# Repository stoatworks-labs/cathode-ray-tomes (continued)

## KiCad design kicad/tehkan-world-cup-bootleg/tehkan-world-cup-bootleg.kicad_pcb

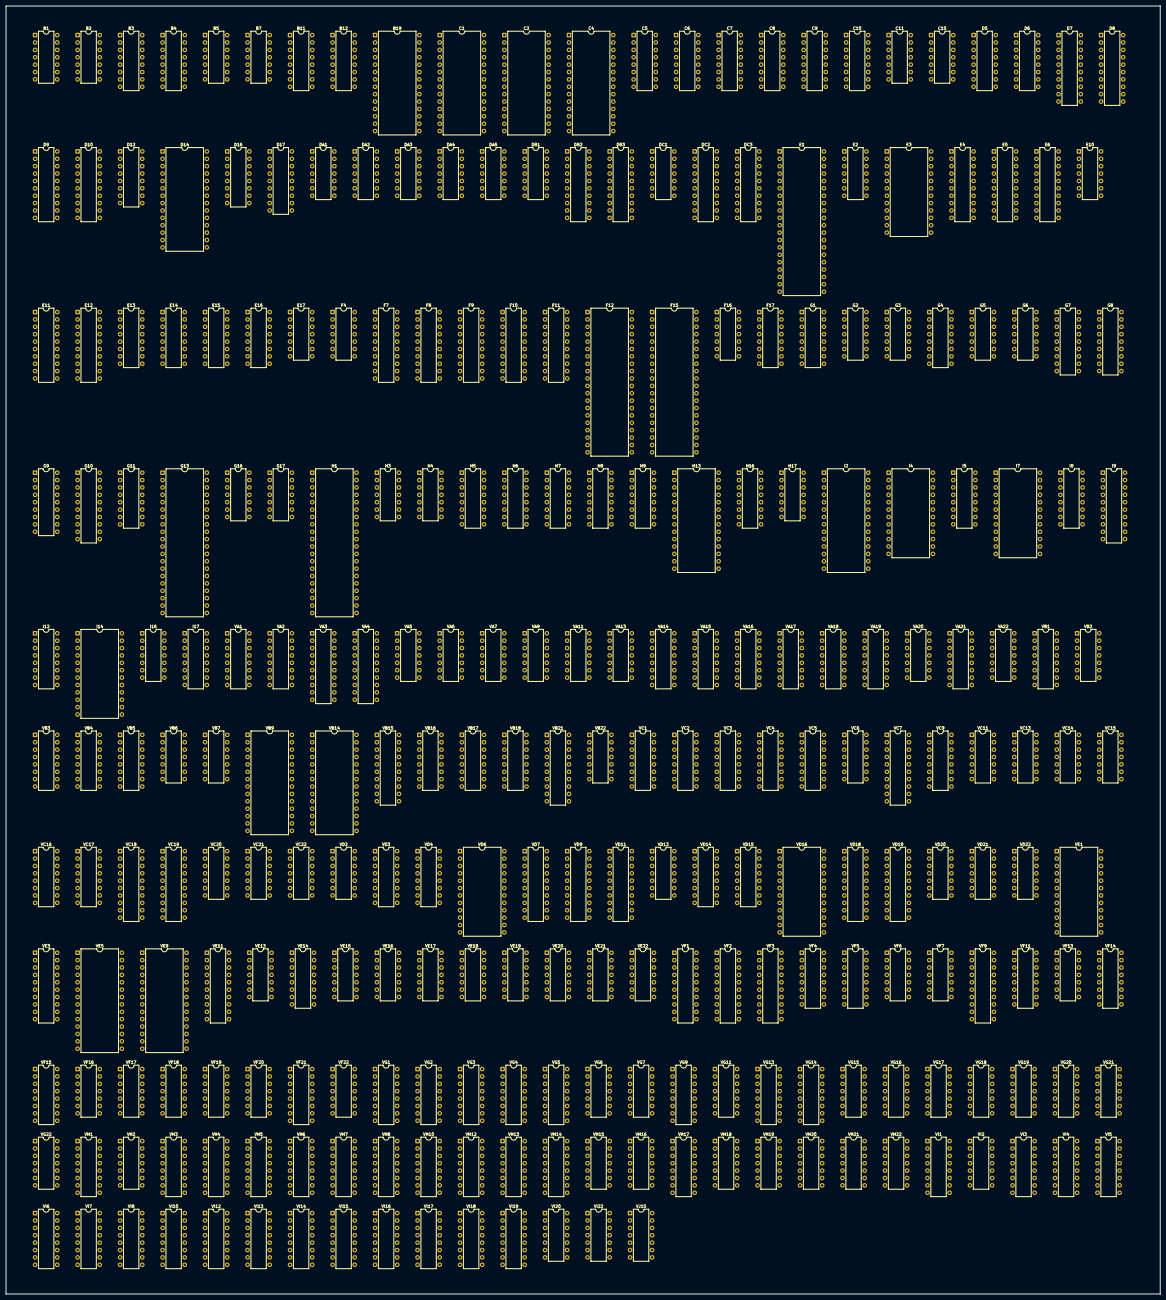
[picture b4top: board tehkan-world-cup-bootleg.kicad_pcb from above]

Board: 2 copper layers, 397.1 x 443.1 mm, 262 parts (0 on the bottom side), 1009 nets, no tracks yet.

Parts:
B1, B2: 74LS74; DIP-14_W7.62mm
B3, B4, B11, B12: 74LS367; DIP-16_W7.62mm
B5, B7: 74LS04; DIP-14_W7.62mm
B19: 27128; DIP-28_W15.24mm
C1, C2, C4: 27128; DIP-28_W15.24mm
C5: 74LS138; DIP-16_W7.62mm
C6: 74LS139; DIP-16_W7.62mm
C7, C8, C9, C10: 74LS157; DIP-16_W7.62mm
C11: 74LS74; DIP-14_W7.62mm
C15: LM324; DIP-14_W7.62mm
D5: 74LS138; DIP-16_W7.62mm
D6: 74LS139; DIP-16_W7.62mm
D7, D8, D9, D10: 74LS244; DIP-20_W7.62mm
D12: 74LS174; DIP-16_W7.62mm
D14: 27128; DIP-28_W15.24mm
D16: 74LS157; DIP-16_W7.62mm
D17: OKI-M5205; DIP-18_W7.62mm
DA1, DA2, DA3: 74LS00; DIP-14_W7.62mm
DA4, DA5: 74LS74; DIP-14_W7.62mm
DB1: 74LS32; DIP-14_W7.62mm
DB2: 74LS373; DIP-20_W7.62mm
DB3: 74LS245; DIP-20_W7.62mm
DC1: 74LS32; DIP-14_W7.62mm
DC2: 74LS373; DIP-20_W7.62mm
DC3: 74LS245; DIP-20_W7.62mm
E1: Z80CPU; DIP-40_W15.24mm
E2, E10: 74LS08; DIP-14_W7.62mm
E3: HM6116P-3; DIP-24_W15.24mm
E4: 74LS245; DIP-20_W7.62mm
E5, E6: 74LS244; DIP-20_W7.62mm
E11, E12: 74LS374; DIP-20_W7.62mm
E13, E14, E15, E16: 74LS191; DIP-16_W7.62mm
E17: 74LS32; DIP-14_W7.62mm
F4: 74LS32; DIP-14_W7.62mm
F7, F8, F9: 74LS273; DIP-20_W7.62mm
F10, F11: 74LS245; DIP-20_W7.62mm
F12, F15: YM2149; DIP-40_W15.24mm
F16: 74LS02; DIP-14_W7.62mm
F17: 74LS367; DIP-16_W7.62mm
G1: 74LS139; DIP-16_W7.62mm
G2, G17: 74LS32; DIP-14_W7.62mm
G3: 74LS08; DIP-14_W7.62mm
G4: 74LS367; DIP-16_W7.62mm
G5: 74LS11; DIP-14_W7.62mm
G6: 74LS74; DIP-14_W7.62mm
G7, G8, G9: MN2114; DIP-18_W7.62mm
G10: 74LS245; DIP-20_W7.62mm
G11: 74LS138; DIP-16_W7.62mm
G13: Z80CPU; DIP-40_W15.24mm
G16: 74LS02; DIP-14_W7.62mm
H1: Z80CPU; DIP-40_W15.24mm
H3, H17: 74LS04; DIP-14_W7.62mm
H4: 74LS74; DIP-14_W7.62mm
H5, H8: 74LS367; DIP-16_W7.62mm
H6, H7: 74LS157; DIP-16_W7.62mm
H9: 74LS138; DIP-16_W7.62mm
H13: 27128; DIP-28_W15.24mm
H16: 74LS139; DIP-16_W7.62mm
I2: 27256; DIP-28_W15.24mm
I4, I7, I14: HM6116P-3; DIP-24_W15.24mm
I5: 74LS157; DIP-16_W7.62mm
I8: 74LS367; DIP-16_W7.62mm
I9: 74LS245; DIP-20_W7.62mm
I12, I17: 74LS257; DIP-16_W7.62mm
I16: 74LS74; DIP-14_W7.62mm
VA1, VA2: 74LS161; DIP-16_W7.62mm
VA3, VA4: 74LS273; DIP-20_W7.62mm
VA5, VA13: 74LS32; DIP-14_W7.62mm
VA6: 74LS86; DIP-14_W7.62mm
VA7, VA9: 74LS11; DIP-14_W7.62mm
VA11, VA22: 74LS08; DIP-14_W7.62mm
VA14: 74LS139; DIP-16_W7.62mm
VA15, VA16, VA17, VA18, VA19: 74LS153; DIP-16_W7.62mm
VA20: 74LS25; DIP-14_W7.62mm
VA21: 74LS157; DIP-16_W7.62mm
VB1: 74LS161; DIP-16_W7.62mm
VB2: 74LS74; DIP-14_W7.62mm
VB3, VB4, VB5: 74LS283; DIP-16_W7.62mm
VB6, VB7: 74LS86; DIP-14_W7.62mm
VB9, VB14: 27256; DIP-28_W15.24mm
VB15, VB21: 74LS273; DIP-20_W7.62mm
VB16, VB17: 74LS157; DIP-16_W7.62mm
VB18: 74LS174; DIP-16_W7.62mm
VB22: 74LS32; DIP-14_W7.62mm
VC1, VC2, VC4, VC5, VC16, VC17: 74LS157; DIP-16_W7.62mm
VC3: 74LS283; DIP-16_W7.62mm
VC6: 74LS08; DIP-14_W7.62mm
VC7, VC19: 74LS273; DIP-20_W7.62mm
VC9: 74LS174; DIP-16_W7.62mm
VC11, VC20: 74LS86; DIP-14_W7.62mm
VC13, VC14: 74LS74; DIP-14_W7.62mm
VC15, VC21, VC22: 74LS32; DIP-14_W7.62mm
VC18: 74LS245; DIP-20_W7.62mm
VD2, VD21: 74LS74; DIP-14_W7.62mm
VD3, VD4: 74LS157; DIP-16_W7.62mm
VD6, VD16: HM6116P-3; DIP-24_W15.24mm
VD7, VD9, VD18, VD19: 74LS273; DIP-20_W7.62mm
VD11: 74LS245; DIP-20_W7.62mm
VD13: 74LS00; DIP-14_W7.62mm
VD14: 74LS175; DIP-16_W7.62mm
VD15: 74LS283; DIP-16_W7.62mm
VD20: 74LS86; DIP-14_W7.62mm
VD22: 74LS08; DIP-14_W7.62mm
VE1: HM6116P-3; DIP-24_W15.24mm
VE3, VE11: 74LS273; DIP-20_W7.62mm
VE5, VE9: 27256; DIP-28_W15.24mm
VE13, VE15: 74LS86; DIP-14_W7.62mm
VE14: 74LS139; DIP-16_W7.62mm
VE16, VE17, VE18: 74LS74; DIP-14_W7.62mm
VE19: 74LS02; DIP-14_W7.62mm
VE20, VE22: 74LS32; DIP-14_W7.62mm
VE21: 74LS04; DIP-14_W7.62mm
VF1, VF2: 74LS245; DIP-20_W7.62mm
VF3, VF9: 74LS273; DIP-20_W7.62mm
VF4, VF5: 74LS161; DIP-16_W7.62mm
VF6, VF7, VF20: 74LS08; DIP-14_W7.62mm
VF11: 74LS157; DIP-16_W7.62mm
VF13: 74LS86; DIP-14_W7.62mm
VF14: 74LS298; DIP-16_W7.62mm
VF15: 74LS194; DIP-16_W7.62mm
VF16: 74LS32; DIP-14_W7.62mm
VF17: 74LS30; DIP-14_W7.62mm
VF18, VF19, VF22: 74LS74; DIP-14_W7.62mm
VF21: 74LS175; DIP-16_W7.62mm
VG1, VG2, VG3: 74LS161; DIP-16_W7.62mm
VG4, VG5, VG13: 74LS157; DIP-16_W7.62mm
VG6, VG7, VG18: 74LS08; DIP-14_W7.62mm
VG9: 74LS174; DIP-16_W7.62mm
VG11: 74LS25; DIP-14_W7.62mm
VG14: 74LS298; DIP-16_W7.62mm
VG15: 74LS10; DIP-14_W7.62mm
VG16: 74LS27; DIP-14_W7.62mm
VG17: 74LS20; DIP-14_W7.62mm
VG19, VG21, VG22: 74LS74; DIP-14_W7.62mm
VG20: 74LS04; DIP-14_W7.62mm
VH1: 74LS161; DIP-16_W7.62mm
VH2, VH15, VH16, VH18, VH19: 74LS86; DIP-14_W7.62mm
VH3, VH4, VH5: 74LS157; DIP-16_W7.62mm
VH6, VH7, VH8, VH10, VH12, VH13, VH14: DIP-16_W7.62mm
VH17: 74LS367; DIP-16_W7.62mm
VH20: 74LS00; DIP-14_W7.62mm
VH21: 74LS393; DIP-14_W7.62mm
VH22: 74LS04; DIP-14_W7.62mm
VI1, VI15, VI16, VI18, VI19: 74LS161; DIP-16_W7.62mm
VI2: 74LS86; DIP-14_W7.62mm
VI3, VI4, VI5: 74LS157; DIP-16_W7.62mm
VI6, VI7, VI8, VI10, VI12, VI13, VI14: DIP-16_W7.62mm
VI17: 74LS367; DIP-16_W7.62mm
VI20: 74LS107; DIP-14_W7.62mm
VI22: 4069; DIP-14_W7.62mm
VJ15: 74LS04; DIP-14_W7.62mm

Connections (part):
/CLK4: H3.3, H3.13, VH22.2
/HB0: H17.5, H17.9
/PXLCLK: F7.11, F8.11, F9.11, VE20.8
/cpu board/4MCK: DA4.3, DA4.11, DA5.3, DA5.11
/cpu board/DB0: B1.2, B1.12, B2.2, B2.12, B3.11, B4.11, B11.13, B12.3, D7.3, D8.3, D9.3, D10.3, DB2.12, DB3.11, E4.11, E5.9, E6.9, E11.3, E12.2
/cpu board/DB1: B3.13, B4.13, B11.9, B12.5, D7.5, D8.5, D9.5, D10.5, DB2.9, DB3.12, E4.12, E5.12, E6.12, E11.4, E12.5
/cpu board/DB2: B3.7, B4.7, B11.11, B12.7, D7.7, D8.7, D9.7, D10.7, DB2.15, DB3.13, E4.13, E5.7, E6.7, E11.7, E12.6
/cpu board/DB3: B3.5, B4.5, B11.3, B12.9, D7.9, D8.9, D9.9, D10.9, DB2.6, DB3.14, E4.14, E5.14, E6.14, E11.8, E12.9
/cpu board/DB4: B4.3, B11.5, D7.12, D8.12, D9.12, D10.12, DB2.16, DB3.15, E4.15, E5.5, E6.5, E11.13, E12.12
/cpu board/DB5: B4.9, B11.7, D7.14, D8.14, D9.14, D10.14, DB2.5, DB3.16, E4.16, E5.16, E6.16, E11.14, E12.15
/cpu board/DB6: D7.16, D8.16, D9.16, D10.16, DB2.19, DB3.17, E4.17, E5.3, E6.3, E11.17, E12.16
/cpu board/DB7: D7.18, D8.18, D9.18, D10.18, DB2.2, DB3.18, E4.18, E5.18, E6.18, E11.18, E12.19
/cpu board/DD0: DB2.13, DB3.9, DC2.13, DC3.9, F10.9, G10.2, I9.2, VA3.3, VA4.3, VC13.2, VC18.9, VD11.9, VF1.9
/cpu board/DD1: DB2.8, DB3.8, DC2.8, DC3.8, F10.8, G10.3, I9.3, VA3.4, VA4.4, VC18.8, VD11.8, VF1.8
/cpu board/DD2: DB2.14, DB3.7, DC2.14, DC3.7, F10.7, G10.4, I9.4, VA3.7, VA4.7, VC18.7, VD11.7, VF1.7
/cpu board/DD3: DB2.7, DB3.6, DC2.7, DC3.6, F10.6, G10.5, I9.5, VA3.8, VA4.8, VC18.6, VD11.6, VF1.6
/cpu board/DD4: DB2.17, DB3.5, DC2.17, DC3.5, F10.5, G10.6, I9.6, VA3.13, VA4.13, VC18.5, VD11.5, VF1.5
/cpu board/DD5: DB2.4, DB3.4, DC2.4, DC3.4, F10.4, G10.7, I9.7, VA3.14, VA4.14, VC18.4, VD11.4, VF1.4
/cpu board/DD6: DB2.18, DB3.3, DC2.18, DC3.3, F10.3, G10.8, I9.8, VA3.17, VA4.17, VC18.3, VD11.3, VF1.3
/cpu board/DD7: DB2.3, DB3.2, DC2.3, DC3.2, F10.2, G10.9, I9.9, VA3.18, VA4.18, VC18.2, VD11.2, VF1.2
/cpu board/DISP: F7.1, F8.1, F9.1, VF20.11
/cpu board/DS0: DC2.12, DC3.11, H1.14, I2.11, I4.9
/cpu board/DS1: DC2.9, DC3.12, H1.15, I2.12, I4.10
/cpu board/DS2: DC2.15, DC3.13, H1.12, I2.13, I4.11
/cpu board/DS3: DC2.6, DC3.14, H1.8, I2.15, I4.13
/cpu board/DS4: DC2.16, DC3.15, H1.7, I2.16, I4.14
/cpu board/DS5: DC2.5, DC3.16, H1.9, I2.17, I4.15
/cpu board/DS6: DC2.19, DC3.17, H1.10, I2.18, I4.16
/cpu board/DS7: DC2.2, DC3.18, H1.13, I2.19, I4.17
/cpu board/HFLIP: B2.9, VC6.12, VC20.1, VC20.9, VE15.12, VG18.12
/cpu board/IO0: C6.4, D10.1, D10.19
/cpu board/IO1: C6.5, D9.1, D9.19
/cpu board/IO2: B12.1, C6.6
/cpu board/IO3: B11.1, B11.15, C6.7
/cpu board/IO4: D6.4, D8.1, D8.19
/cpu board/IO5: D6.5, D7.1, D7.19
/cpu board/IO7: B4.1, B4.15, D6.7
/cpu board/IO/~DIP1: B3.1, B3.15, D5.7
/cpu board/IO/~DIP2: D5.11, E6.1, E6.19
/cpu board/IO/~DIP3: D5.10, E5.1, E5.19
/cpu board/MA0: C6.2, C6.14, D6.2, D6.14, H5.3, H7.2
/cpu board/MA1: C6.3, C6.13, D6.3, D6.13, H5.5, H7.5
/cpu board/MA2: H5.11, H7.11
/cpu board/MA3: H5.13, H7.14
/cpu board/MA4: C5.1, D5.1, H5.7, H6.2
/cpu board/MA5: C5.2, D5.2, H5.9, H6.5
/cpu board/MA6: C5.3, D5.3, G4.13, H6.11
/cpu board/MA7: G4.3, H6.14
/cpu board/MA8: G4.5, I5.2
/cpu board/MA9: G4.7, I5.5
/cpu board/MA10: G4.9, I5.11
/cpu board/MxC8: G3.13, H9.14, I12.2, VA9.5
/cpu board/MxD0: H9.13, I12.5, VA9.4
/cpu board/MxD8: H9.12, I12.11, VA7.5
/cpu board/MxE0: H9.11, I12.14, VA7.4
/cpu board/MxE8: H9.10, I17.2, VA7.3
/cpu board/PA0: G7.5, G8.5, G9.5, VA15.7
/cpu board/PA1: G7.6, G8.6, G9.6, VA15.9
/cpu board/PA2: G7.7, G8.7, G9.7, VA16.7
/cpu board/PA3: G7.4, G8.4, G9.4, VA16.9
/cpu board/PA4: G7.3, G8.3, G9.3, VA17.7
/cpu board/PA5: G7.2, G8.2, G9.2, VA17.9
/cpu board/PA6: G7.1, G8.1, G9.1, VA18.7
/cpu board/PA7: G7.17, G8.17, G9.17, VA18.9
/cpu board/PA8: G7.16, G8.16, G9.16, VA19.7
/cpu board/PA9: G7.15, G8.15, G9.15, VA19.9
/cpu board/SA0: H1.30, H7.3, I2.10, I4.8
/cpu board/SA1: H1.31, H7.6, I2.9, I4.7
/cpu board/SA2: H1.32, H7.10, I2.8, I4.6
/cpu board/SA3: H1.33, H7.13, I2.7, I4.5
/cpu board/SA4: H1.34, H6.3, I2.6, I4.4
/cpu board/SA5: H1.35, H6.6, I2.5, I4.3
/cpu board/SA6: H1.36, H6.10, I2.4, I4.2
/cpu board/SA7: H1.37, H6.13, I2.3, I4.1
/cpu board/SA8: H1.38, I2.25, I4.23, I5.3
/cpu board/SA9: H1.39, I2.24, I4.22, I5.6
/cpu board/SA10: H1.40, I2.21, I4.19, I5.10
/cpu board/SA11: G11.1, H1.1, I2.23
/cpu board/SA12: G11.2, H1.2, I2.2
/cpu board/SA13: G11.3, H1.3, I2.26
/cpu board/SA14: G1.14, H1.4, I2.27
/cpu board/SA15: G1.13, H1.5
/cpu board/SHAB0: H8.5, VA14.2, VC1.2, VC5.2, VC17.2, VC21.10, VE21.13
/cpu board/SHAB1: H8.9, VA14.3, VA15.6, VC1.5, VC5.5, VC17.5
/cpu board/SHAB2: H8.13, VA15.10, VC1.11, VC5.11, VC17.11
/cpu board/SHAB3: H8.11, VA16.6, VC1.14, VC5.14, VC17.14
/cpu board/SHAB4: H8.3, VA16.10, VC2.2, VC4.2, VC16.2
/cpu board/SHAB5: H8.7, VA17.6, VC2.5, VC4.5, VC16.5
/cpu board/SHAB6: I8.3, VA17.10, VC2.11, VC4.11, VC16.11
/cpu board/SHAB7: I8.11, VA18.6, VC2.14, VC4.14, VC16.14
/cpu board/SHAB8: I8.5, VA18.10, VB17.2, VD3.2, VD4.2
/cpu board/SHAB9: I8.9, VA19.6, VB17.5, VD3.5, VD4.5
/cpu board/SHAB10: I8.7, VA19.10, VB17.11, VD4.11, VD13.4, VE20.13
/cpu board/SH~RD: F10.1, G10.1, I8.13, VA22.2, VB17.14, VC18.1, VD3.11, VD4.14, VD11.1, VF1.1
/cpu board/SSD0: I12.7, VE21.1, VE22.2, VE22.4
/cpu board/SSD8: I12.9, VC21.2, VC22.1, VE21.11
/cpu board/SSE0: I12.12, VC15.9, VD13.12
/cpu board/SSE8: I17.4, VE19.8, VE20.12
/cpu board/SxC8: G3.10, G11.14, I12.3, VA7.9
/cpu board/SxD0: G11.13, I12.6, VA7.10
/cpu board/SxD8: G11.12, I12.10, VA7.2
/cpu board/SxE0: G11.11, I12.13, VA7.1
/cpu board/SxE8: G11.10, I17.3, VA7.13
/cpu board/VBL: I16.3, VD22.10, VD22.12, VF20.12, VG21.9
/cpu board/VFLIP: B2.5, VA6.1, VG18.5
/cpu board/WDOG: D5.9, VH20.2
/cpu board/main CPU/A0: C1.10, C2.10, C4.10, E1.30, E3.8, H5.2
/cpu board/main CPU/A1: C1.9, C2.9, C4.9, E1.31, E3.7, H5.4
/cpu board/main CPU/A2: C1.8, C2.8, C4.8, E1.32, E3.6, H5.12
/cpu board/main CPU/A3: C1.7, C2.7, C4.7, E1.33, E3.5, H5.14
/cpu board/main CPU/A4: C1.6, C2.6, C4.6, E1.34, E3.4, H5.6
/cpu board/main CPU/A5: C1.5, C2.5, C4.5, E1.35, E3.3, H5.10
/cpu board/main CPU/A6: C1.4, C2.4, C4.4, E1.36, E3.2, G4.14
/cpu board/main CPU/A7: C1.3, C2.3, C4.3, E1.37, E3.1, G4.2
/cpu board/main CPU/A8: C1.25, C2.25, C4.25, E1.38, E3.23, G4.4
/cpu board/main CPU/A9: C1.24, C2.24, C4.24, E1.39, E3.22, G4.6
/cpu board/main CPU/A10: C1.21, C2.21, C4.21, E1.40, E3.19, G4.10
/cpu board/main CPU/A11: C1.23, C2.23, C4.23, E1.1, H9.1
/cpu board/main CPU/A12: C1.2, C2.2, C4.2, E1.2, H9.2
/cpu board/main CPU/A13: C1.26, C2.26, C4.26, E1.3, H9.3
/cpu board/main CPU/A14: E1.4, G1.2
/cpu board/main CPU/A15: E1.5, G1.3
/cpu board/main CPU/D0: C1.11, C2.11, C4.11, E1.14, E3.9, E4.9
/cpu board/main CPU/D1: C1.12, C2.12, C4.12, E1.15, E3.10, E4.8
/cpu board/main CPU/D2: C1.13, C2.13, C4.13, E1.12, E3.11, E4.7
/cpu board/main CPU/D3: C1.15, C2.15, C4.15, E1.8, E3.13, E4.6
/cpu board/main CPU/D4: C1.16, C2.16, C4.16, E1.7, E3.14, E4.5
/cpu board/main CPU/D5: C1.17, C2.17, C4.17, E1.9, E3.15, E4.4
/cpu board/main CPU/D6: C1.18, C2.18, C4.18, E1.10, E3.16, E4.3
/cpu board/main CPU/D7: C1.19, C2.19, C4.19, E1.13, E3.17, E4.2
/cpu board/main CPU/MMx0: C1.20, G1.4
/cpu board/main CPU/MMx4: C2.20, G1.5
/cpu board/main CPU/MMx8: C4.20, G1.6
/cpu board/main CPU/MMxC: F4.12, G1.7, H9.5
/cpu board/main CPU/MMxC0: E3.18, H3.11, H9.15
/cpu board/main CPU/MMxF8: C5.5, D5.5, H9.7
/cpu board/main CPU/~IORQ: E1.20, G2.1
/cpu board/main CPU/~M1: E1.27, G2.2
/cpu board/main CPU/~MREQ: E1.19, G2.13
/cpu board/main CPU/~RD: C1.22, C2.22, C4.22, E1.21, E3.20, G4.12
/cpu board/main CPU/~RFSH: E1.28, H3.1
/cpu board/main CPU/~S2M: D5.13, E12.1
/cpu board/main CPU/~SUBRST: B1.9, H1.26
/cpu board/main CPU/~WR: E1.22, E3.21, G3.2
/cpu board/palette/B0: F9.8, F9.13, F10.15, G9.14
/cpu board/palette/B1: F9.7, F9.14, F10.16, G9.13
/cpu board/palette/B2: F9.4, F9.17, F10.17, G9.12
/cpu board/palette/B3: F9.3, F9.18, F10.18, G9.11
/cpu board/palette/G0: F7.18, F8.18, G7.14, G10.18
/cpu board/palette/G1: F7.17, F8.17, G7.13, G10.17
/cpu board/palette/G2: F7.14, F8.14, G7.12, G10.16
/cpu board/palette/G3: F7.13, F8.13, G7.11, G10.15
/cpu board/palette/R0: F7.8, F8.8, G8.14, G10.14
/cpu board/palette/R1: F7.7, F8.7, G8.13, G10.13
/cpu board/palette/R2: F7.4, F8.4, G8.12, G10.12
/cpu board/palette/R3: F7.3, F8.3, G8.11, G10.11
/cpu board/shared/D0: I7.9, I9.18
/cpu board/shared/D1: I7.10, I9.17
/cpu board/shared/D2: I7.11, I9.16
/cpu board/shared/D3: I7.13, I9.15
/cpu board/shared/D4: I7.14, I9.14
/cpu board/shared/D5: I7.15, I9.13
/cpu board/shared/D6: I7.16, I9.12
/cpu board/shared/D7: I7.17, I9.11
/cpu board/shared/RAM_~CS: I7.18, I9.19, I12.4
/cpu board/shared/SHA0: H7.4, H8.4, I7.8
/cpu board/shared/SHA1: H7.7, H8.10, I7.7
/cpu board/shared/SHA2: H7.9, H8.14, I7.6
/cpu board/shared/SHA3: H7.12, H8.12, I7.5
/cpu board/shared/SHA4: H6.4, H8.2, I7.4
/cpu board/shared/SHA5: H6.7, H8.6, I7.3
/cpu board/shared/SHA6: H6.9, I7.2, I8.2
/cpu board/shared/SHA7: H6.12, I7.1, I8.12
/cpu board/shared/SHA8: I5.4, I7.23, I8.4
/cpu board/shared/SHA9: I5.7, I7.22, I8.10
/cpu board/shared/SHA10: I5.9, I7.19, I8.6
/cpu board/shared/SH~OE: I5.12, I7.20, I8.14, I9.1
/cpu board/sound/A0: F17.4, G13.30, H13.10, I14.8
/cpu board/sound/A1: F17.10, G13.31, H13.9, I14.7
/cpu board/sound/A2: G13.32, H13.8, I14.6
/cpu board/sound/A3: G13.33, H13.7, I14.5
/cpu board/sound/A4: G13.34, H13.6, I14.4
/cpu board/sound/A5: G13.35, H13.5, I14.3
/cpu board/sound/A6: G13.36, H13.4, I14.2
/cpu board/sound/A7: G13.37, H13.3, I14.1
/cpu board/sound/A8: G13.38, H13.25, I14.23
/cpu board/sound/A9: G13.39, H13.24, I14.22
/cpu board/sound/A10: G13.40, H13.21, I14.19
/cpu board/sound/A11: G13.1, H13.23
/cpu board/sound/A12: G13.2, H13.2
/cpu board/sound/A13: G13.3, H13.26
/cpu board/sound/A14: G13.4, H16.14
/cpu board/sound/A15: G13.5, H16.13
/cpu board/sound/AB0: F16.11, F17.5, G16.11, H16.2
/cpu board/sound/AB1: E17.9, F17.9, H16.3, H17.13
/cpu board/sound/ABC1: F12.29, F16.1
/cpu board/sound/ABC2: F12.28, F16.13
/cpu board/sound/ABDIR: F12.27, F16.4
/cpu board/sound/BBC1: F15.29, G16.1
/cpu board/sound/BBC2: F15.28, G16.13
/cpu board/sound/BBDIR: F15.27, G16.4
/cpu board/sound/CNT0: D14.9, E16.2, F12.20
/cpu board/sound/CNT1: D14.8, E16.6, F12.19
/cpu board/sound/CNT2: D14.7, E16.7, F12.18
/cpu board/sound/CNT3: D14.6, E15.3, F12.17
/cpu board/sound/CNT4: D14.5, E15.2, F12.16
/cpu board/sound/CNT5: D14.4, E15.6, F12.15
/cpu board/sound/CNT6: D14.3, E15.7, F12.14
/cpu board/sound/CNT7: D14.25, E14.3, F12.13
/cpu board/sound/CNT8: D14.24, E14.2, F12.12
/cpu board/sound/CNT9: D14.21, E14.6, F12.11
/cpu board/sound/CNT10: D14.23, E14.7, F12.10
/cpu board/sound/CNT11: D14.2, E13.3, F12.9
/cpu board/sound/CNT12: D14.26, E13.2, F12.8
/cpu board/sound/CNT13: D14.27, F12.7
/cpu board/sound/CPUCLK: G13.6, H17.8
/cpu board/sound/D0: F11.2, F12.37, F15.37, G13.14, H13.11, I14.9
/cpu board/sound/D1: F11.3, F12.36, F15.36, G13.15, H13.12, I14.10
/cpu board/sound/D2: F11.4, F12.35, F15.35, G13.12, H13.13, I14.11
/cpu board/sound/D3: F11.5, F12.34, F15.34, G13.8, H13.15, I14.13
/cpu board/sound/D4: F11.6, F12.33, F15.33, G13.7, H13.16, I14.14
/cpu board/sound/D5: F11.7, F12.32, F15.32, G13.9, H13.17, I14.15
/cpu board/sound/D6: F11.8, F12.31, F15.31, G13.10, H13.18, I14.16
/cpu board/sound/D7: F11.9, F12.30, F15.30, G13.13, H13.19, I14.17
/cpu board/sound/DB0: C11.2, D12.14, E11.2, E12.3, F11.18
/cpu board/sound/DB1: D12.3, E11.5, E12.4, F11.17
/cpu board/sound/DB2: D12.4, E11.6, E12.7, F11.16
/cpu board/sound/DB3: D12.13, E11.9, E12.8, F11.15
/cpu board/sound/DB4: E11.12, E12.13, F11.14
/cpu board/sound/DB5: E11.15, E12.14, F11.13
/cpu board/sound/DB6: E11.16, E12.17, F11.12
/cpu board/sound/DB7: E11.19, E12.18, F11.11
/cpu board/sound/IOA1: E17.8, G16.3, G16.5, G16.12
/cpu board/sound/IO~A1: E17.11, F16.3, F16.5, F16.12
/cpu board/sound/MMx0: H13.20, H16.12
/cpu board/sound/MMx4: H16.11, I14.18
/cpu board/sound/MMx8: E10.12, E17.4, H16.10
/cpu board/sound/MMxC: E10.13, F4.2, G17.13, H16.9
/cpu board/sound/PCM/A0: D14.10, E16.3
/cpu board/sound/PCM/RC: E16.14, E17.3
/cpu board/sound/PCM/RC0: E15.14, E16.13
/cpu board/sound/PCM/RC1: E14.14, E15.13
/cpu board/sound/PCM/RC2: E13.14, E14.13
/cpu board/sound/PCM/~EN: C11.6, D14.20, D16.15, D17.15, E13.4, E14.4, E15.4, E16.4, E17.2
/cpu board/sound/PCM/~VCK: C11.11, D17.14
/cpu board/sound/PCMSND: C15.12, D17.10
/cpu board/sound/PSGCLK: F12.22, F15.22, I16.9
/cpu board/sound/SMP0: E16.15, F15.21
/cpu board/sound/SMP1: E16.1, F15.20
/cpu board/sound/SMP2: E16.10, F15.19
/cpu board/sound/SMP3: E16.9, F15.18
/cpu board/sound/SMP4: E15.15, F15.17
/cpu board/sound/SMP5: E15.1, F15.16
/cpu board/sound/SMP6: E15.10, F15.15
/cpu board/sound/SMP7: E15.9, F15.14
/cpu board/sound/SMP8: E14.15, F15.13
/cpu board/sound/SMP9: E14.1, F15.12
/cpu board/sound/SMP10: E14.10, F15.11
/cpu board/sound/SMP11: E14.9, F15.10
/cpu board/sound/SMP12: E13.15, F15.9
/cpu board/sound/SMP13: E13.1, F15.8
/cpu board/sound/SMP14: E13.10, F15.7
/cpu board/sound/SMP15: E13.9, F15.6
/cpu board/sound/analog/REF: C15.3, C15.5
/cpu board/sound/~GAINSET: D12.9, H16.6
/cpu board/sound/~IORQB: E17.10, E17.12, F17.13
/cpu board/sound/~IORQ: F17.14, G13.20, G17.9
/cpu board/sound/~M1: G13.27, G17.10
/cpu board/sound/~MREQ: G13.19, G17.1
/cpu board/sound/~NMICLR: E2.9, H16.7
/cpu board/sound/~PCMCTL: C11.3, H16.5
/cpu board/sound/~PCMSET: E13.11, E14.11, E15.11, E16.11, H16.4
/cpu board/sound/~RDB: F4.1, F11.1, F16.2, F17.3, G16.2, H13.22, I14.20
/cpu board/sound/~RD: F17.2, G13.21
/cpu board/sound/~RFSH: G13.28, H17.1
/cpu board/sound/~WRB: E17.5, F16.6, F17.11, G16.6, G17.12, I14.21
/cpu board/sound/~WR: F17.12, G13.22
/cpu board/sub CPU/MMx0: G1.12, G3.5
/cpu board/sub CPU/MMx4: G1.11, G3.4
/cpu board/sub CPU/MMxC: G1.9, G11.5
/cpu board/sub CPU/MMxC0: G11.15, I4.18
/cpu board/sub CPU/~IORQ: G2.4, H1.20
/cpu board/sub CPU/~M1: G2.5, H1.27
/cpu board/sub CPU/~MREQ: G2.9, H1.19
/cpu board/sub CPU/~RFSH: H1.28, H3.5
/cpu board/sub CPU/~ROM: G3.6, I2.20
/cpu board/~CSEL: G5.1, VC21.9, VC21.12, VC22.3, VD22.2, VD22.5
/cpu board/~EGCONT: DA3.6, VE20.5
/cpu board/~FIXCS: G5.2, VC18.19, VC21.5, VE22.3
/cpu board/~GBWE: G7.10, G8.10, VB22.6
/cpu board/~GB_CS: G10.19, VB22.11
/cpu board/~MLE: DC1.1, G3.11
/cpu board/~MNSEL: DA1.13, DA3.1, DA5.4, VA9.6, VA13.5, VA13.10
/cpu board/~MSEL: DA3.8, DA3.12, DA4.2, DB1.1, DB1.10, DB1.12, DC1.2, H6.1, H7.1, I5.1, I12.1, I17.1, VA13.9
/cpu board/~MSW: DA1.3, VA11.9
/cpu board/~MUTE: B1.5, C11.1, D12.1, F12.23, F15.23, G13.26
/cpu board/~MWR: C5.4, DB1.13, G3.3, I17.5
/cpu board/~PCBSEL: G5.13, VA22.6
/cpu board/~RDB: D5.4, DB1.9, E4.1, G4.11, I5.14
/cpu board/~REDWE: G9.10, VB22.3
/cpu board/~RST: B1.1, B1.13, B2.1, B2.13, E1.26, VH22.8
/cpu board/~R_CS: F10.19, VB22.8
/cpu board/~SBSEL': DA2.1, DA2.9, DA5.10, VA7.8, VA13.1, VA13.13
/cpu board/~SHEN: I12.15, I17.15, VE20.6
/cpu board/~SHWE: DA2.11, G17.4
/cpu board/~SHWR: G17.6, I7.21, VA5.1, VA22.1, VB22.2, VB22.5, VC15.5, VC21.4, VD3.14, VE19.9
/cpu board/~SLE: DC1.9, G3.8
/cpu board/~SND: C5.13, E11.11, G6.11
/cpu board/~SRD: DC1.13, H1.21, I2.22, I4.20, I5.13
/cpu board/~SSEL: DA3.10, DA3.11, DA4.12, DB1.5, DC1.4, DC1.10, DC1.12, VA13.12
/cpu board/~SSW: DA2.6, VA11.4
/cpu board/~SWR: DC1.5, H1.22, I4.21, I17.6
/cpu board/~VIDEO_CS: G3.9, G3.12, G5.12
/video board/C22_13: VC22.13, VD21.5, VD22.9
/video board/GHFLIP: VA6.13, VB7.1, VB7.12, VC6.11, VC11.2, VC11.5, VC11.9, VC11.12, VD15.7
/video board/HB0: VA6.9, VB2.4, VC1.3, VD2.11, VD15.6, VF18.12, VF21.4, VG4.1, VG5.1, VG15.1, VG22.11, VH17.9
/video board/HB0*: VC20.12, VF18.3, VF21.2, VG16.4
/video board/HB1: VA6.5, VC1.6, VD13.1, VD13.2, VD15.2, VF19.11, VF21.5, VG15.13, VH17.11
/video board/HB1*: VC19.11, VF21.7, VF22.3, VH20.13
/video board/HB2: VA20.10, VD15.15, VE13.10, VF21.12, VG20.13, VH17.13
/video board/HB3: VA20.12, VC22.4, VD15.11, VE13.4, VF17.1, VH17.7
/video board/HB4: VA20.13, VD2.2, VF13.4, VF17.6, VH17.5
/video board/HB5: VE13.1, VF17.5, VG17.4, VG17.12, VH17.3
/video board/HB6: VC15.1, VF13.13, VF17.4, VG17.2, VG17.13, VI17.9
/video board/HB7: VC6.2, VG17.1, VI17.11
/video board/HB8*: VD21.2, VF18.2, VG22.5, VG22.12
/video board/HBCLK: VA5.10, VD14.9, VE20.10, VF15.11, VF21.9, VG16.5, VG16.13, VH1.2, VI1.2, VI17.5
/video board/HBL: VC15.2, VC22.12, VF19.3, VG16.1, VG18.8
/video board/HF0: VC6.5, VH18.11
/video board/HF1: VB3.5, VH18.8
/video board/HF2: VB3.3, VH18.6
/video board/HF3: VB3.14, VC17.3, VH18.3
/video board/HF4: VB3.12, VC17.6, VH19.11
/video board/HF5: VB5.5, VC17.10, VH19.8
/video board/HF6: VB5.3, VC17.13, VH19.6
/video board/HF7: VC16.3, VH19.3
/video board/HX2: VC5.3, VC14.2, VD7.11, VD14.10, VD19.11
/video board/OSCLK: VA1.2, VA2.2, VB1.2, VG17.8
/video board/OXCLK: VE18.3, VG16.9, VG20.2
/video board/PH1: VD18.11, VF22.5, VG22.3
/video board/SCRH0: VB7.10, VD14.6
/video board/SCRH1: VB7.4, VC6.10, VC14.6
/video board/SCRH2: VB6.13, VC14.9, VC15.13
/video board/V0: VD20.5, VG19.9, VH16.13, VI16.7, VI16.10
/video board/V1: VD20.2, VH16.10, VI16.14
/video board/V2: VC20.5, VH16.4, VI16.13
/video board/V3: VH16.1, VI16.12
/video board/V4: VG21.11, VH15.13, VI16.11
/video board/V5: VH15.10, VH20.9, VI15.14
/video board/V6: VF20.9, VH15.4, VI15.13
/video board/V7: VF20.10, VH15.1, VI15.12
/video board/V8: VG18.2, VI15.11
/video board/VF0: VB4.6, VH3.3, VH16.11
/video board/VF1: VB4.2, VH3.6, VH16.8
/video board/VF2: VB4.15, VH3.10, VH16.6
/video board/VF3: VB4.11, VC16.6, VH3.13, VH16.3
/video board/VF4: VC3.6, VC16.10, VH15.11, VI3.3
/video board/VF5: VC3.2, VC16.13, VH15.8, VI3.6
/video board/VF6: VB17.3, VC3.15, VH15.6, VI3.10
/video board/VF7: VB17.6, VC3.11, VH15.3, VI3.13
/video board/X6B: VF14.11, VF18.11, VG14.11, VG15.2, VG17.9, VI17.3
/video board/address decoder/VC13_9: VC13.9, VC15.10
/video board/address decoder/~AB0: VC21.13, VE21.12
/video board/address decoder/~BUSY: VA11.3, VA13.2, VA13.4
/video board/color mixer/FIX0: VA15.5, VA20.5, VA21.4
/video board/color mixer/FIX1: VA15.11, VA20.4, VA21.7
/video board/color mixer/FIX2: VA16.5, VA20.2, VA21.9
/video board/color mixer/FIX3: VA16.11, VA20.1, VA21.12
/video board/color mixer/FIX4: VA17.5, VB18.2
/video board/color mixer/FIX5: VA17.11, VB18.5
/video board/color mixer/FIX6: VA18.5, VB18.7
/video board/color mixer/FIX7: VA18.11, VB18.10
/video board/color mixer/OBJ0: VA15.4, VG11.9, VG14.15
/video board/color mixer/OBJ1: VA15.12, VG11.10, VG14.14
/video board/color mixer/OBJ2: VA16.4, VG11.12, VG14.13
/video board/color mixer/OBJ3: VA16.12, VG11.13, VG14.12
/video board/color mixer/OBJ4: VA17.4, VF14.15
/video board/color mixer/OBJ5: VA17.12, VF14.14
/video board/color mixer/OBJ6: VA18.4, VF14.13
/video board/color mixer/S0: VA15.14, VA16.14, VA17.14, VA18.14, VA19.14, VD22.3
/video board/color mixer/S1: VA15.2, VA16.2, VA17.2, VA18.2, VA19.2, VD22.6
/video board/color mixer/SCR0: VA15.3, VB16.4
/video board/color mixer/SCR1: VA15.13, VB16.7
/video board/color mixer/SCR2: VA16.3, VB16.9
/video board/color mixer/SCR3: VA16.13, VB16.12
/video board/color mixer/SCR4: VA17.3, VC9.2
/video board/color mixer/SCR5: VA17.13, VC9.5
/video board/color mixer/SCR6: VA18.3, VC9.7
/video board/color mixer/SCR7: VA18.13, VC9.10
/video board/color mixer/~FIXOPA: VA20.6, VD22.4, VE21.9
/video board/color mixer/~FIXPRIO: VB18.12, VE21.5
/video board/color mixer/~OBJOPA: VE22.10, VE22.13, VG11.8
/video board/fix/AH0: B19.10, VD20.11
/video board/fix/AH1: B19.9, VD20.8
/video board/fix/AV0: B19.8, VD20.6
/video board/fix/AV1: B19.7, VD20.3
/video board/fix/AV2: B19.6, VC20.6
/video board/fix/CODE0: B19.5, VC19.2
/video board/fix/CODE1: B19.4, VC19.5
/video board/fix/CODE2: B19.3, VC19.6
/video board/fix/CODE3: B19.25, VC19.9
/video board/fix/CODE4: B19.24, VC19.12
/video board/fix/CODE5: B19.21, VC19.15
/video board/fix/CODE6: B19.23, VC19.16
/video board/fix/CODE7: B19.2, VC19.19
/video board/fix/CODE8: B19.26, VD18.12
/video board/fix/D0: VC18.11, VD16.9, VD18.3, VD19.3
/video board/fix/D1: VC18.12, VD16.10, VD18.4, VD19.4
/video board/fix/D2: VC18.13, VD16.11, VD18.7, VD19.7
/video board/fix/D3: VC18.14, VD16.13, VD18.8, VD19.8
/video board/fix/D4: VC18.15, VD16.14, VD18.13, VD19.13
/video board/fix/D5: VC18.16, VD16.15, VD18.14, VD19.14
/video board/fix/D6: VC18.17, VD16.16, VD18.17, VD19.17
/video board/fix/D7: VC18.18, VD16.17, VD18.18, VD19.18
/video board/fix/HF: VB18.14, VC20.2, VD18.16
/video board/fix/HF*: VB18.15, VC20.10
/video board/fix/VB21_11: VB21.11, VF21.3
/video board/fix/VF: VA6.2, VD18.19
/video board/object/OCK0: VA2.14, VF13.10, VF17.3
/video board/object/OCK1: VA2.13, VF13.1, VF17.2, VG15.5
/video board/object/P0: VF6.9, VF7.9, VF11.4, VG11.5
/video board/object/P1: VF6.5, VF7.5, VF11.7, VG11.4
/video board/object/P2: VF6.2, VF7.2, VF11.9, VG11.2
/video board/object/P3: VF11.12, VG6.12, VG7.12, VG11.1
/video board/object/P4: VG6.9, VG7.9, VG9.2
/video board/object/P5: VG6.5, VG7.5, VG9.5
/video board/object/P6: VG6.2, VG7.2, VG9.7
/video board/object/QA0: VG14.3, VI14.14
/video board/object/QA1: VG14.4, VI13.14
/video board/object/QA2: VG14.9, VI12.14
/video board/object/QA3: VG14.7, VI10.14
/video board/object/QA4: VF14.3, VI8.14
/video board/object/QA5: VF14.4, VI7.14
/video board/object/QA6: VF14.9, VI6.14
/video board/object/QB0: VG14.2, VH14.14
/video board/object/QB1: VG14.1, VH13.14
/video board/object/QB2: VG14.5, VH12.14
/video board/object/QB3: VG14.6, VH10.14
/video board/object/QB4: VF14.2, VH8.14
/video board/object/QB5: VF14.1, VH7.14
/video board/object/QB6: VF14.5, VH6.14
/video board/object/R0: VH3.4, VH4.3, VI4.3
/video board/object/R1: VH3.7, VH4.6, VI4.6
/video board/object/R2: VH3.9, VH4.10, VI4.10
/video board/object/R3: VH3.12, VH4.13, VI4.13
/video board/object/R4: VH5.3, VI3.4, VI5.3
/video board/object/R5: VH5.6, VI3.7, VI5.6
/video board/object/R6: VH5.10, VI3.9, VI5.10
/video board/object/R7: VH5.13, VI3.12, VI5.13
/video board/object/X0: VG4.4, VH4.2, VI4.2
/video board/object/X1: VG4.7, VH4.5, VI4.5
/video board/object/X2: VG4.9, VH4.11, VI4.11
/video board/object/X3: VG4.12, VH4.14, VI4.14
/video board/object/X4: VG5.4, VH5.2, VI5.2
/video board/object/X5: VG5.7, VH5.5, VI5.5
/video board/object/X6: VG5.9, VH5.11, VI5.11
/video board/object/X7: VG5.12, VH5.14, VI5.14
/video board/object/Y6*: VF16.12, VI17.13
/video board/object/frame buffer A/A0: VI4.4, VI6.5, VI7.5, VI8.5, VI10.5, VI12.5, VI13.5, VI14.5
/video board/object/frame buffer A/A1: VI4.7, VI6.7, VI7.7, VI8.7, VI10.7, VI12.7, VI13.7, VI14.7
/video board/object/frame buffer A/A2: VI4.9, VI6.6, VI7.6, VI8.6, VI10.6, VI12.6, VI13.6, VI14.6
/video board/object/frame buffer A/A3: VI4.12, VI6.12, VI7.12, VI8.12, VI10.12, VI12.12, VI13.12, VI14.12
/video board/object/frame buffer A/A4: VI5.4, VI6.11, VI7.11, VI8.11, VI10.11, VI12.11, VI13.11, VI14.11
/video board/object/frame buffer A/A5: VI5.7, VI6.10, VI7.10, VI8.10, VI10.10, VI12.10, VI13.10, VI14.10
/video board/object/frame buffer A/A6: VI5.9, VI6.13, VI7.13, VI8.13, VI10.13, VI12.13, VI13.13, VI14.13
/video board/object/frame buffer A/A7: VI5.12, VI6.9, VI7.9, VI8.9, VI10.9, VI12.9, VI13.9, VI14.9
/video board/object/frame buffer A/D0: VF6.8, VI14.2
/video board/object/frame buffer A/D1: VF6.6, VI13.2
/video board/object/frame buffer A/D2: VF6.3, VI12.2
/video board/object/frame buffer A/D3: VG6.11, VI10.2
/video board/object/frame buffer A/D4: VG6.8, VI8.2
/video board/object/frame buffer A/D5: VG6.6, VI7.2
/video board/object/frame buffer A/D6: VG6.3, VI6.2
/video board/object/frame buffer A/~WR*: VF6.11, VI6.3, VI7.3, VI8.3, VI10.3, VI12.3, VI13.3, VI14.3
/video board/object/frame buffer B/A0: VH4.4, VH6.5, VH7.5, VH8.5, VH10.5, VH12.5, VH13.5, VH14.5
/video board/object/frame buffer B/A1: VH4.7, VH6.7, VH7.7, VH8.7, VH10.7, VH12.7, VH13.7, VH14.7
/video board/object/frame buffer B/A2: VH4.9, VH6.6, VH7.6, VH8.6, VH10.6, VH12.6, VH13.6, VH14.6
/video board/object/frame buffer B/A3: VH4.12, VH6.12, VH7.12, VH8.12, VH10.12, VH12.12, VH13.12, VH14.12
/video board/object/frame buffer B/A4: VH5.4, VH6.11, VH7.11, VH8.11, VH10.11, VH12.11, VH13.11, VH14.11
/video board/object/frame buffer B/A5: VH5.7, VH6.10, VH7.10, VH8.10, VH10.10, VH12.10, VH13.10, VH14.10
/video board/object/frame buffer B/A6: VH5.9, VH6.13, VH7.13, VH8.13, VH10.13, VH12.13, VH13.13, VH14.13
/video board/object/frame buffer B/A7: VH5.12, VH6.9, VH7.9, VH8.9, VH10.9, VH12.9, VH13.9, VH14.9
/video board/object/frame buffer B/D0: VF7.8, VH14.2
/video board/object/frame buffer B/D1: VF7.6, VH13.2
/video board/object/frame buffer B/D2: VF7.3, VH12.2
/video board/object/frame buffer B/D3: VG7.11, VH10.2
/video board/object/frame buffer B/D4: VG7.8, VH8.2
/video board/object/frame buffer B/D5: VG7.6, VH7.2
/video board/object/frame buffer B/D6: VG7.3, VH6.2
/video board/object/frame buffer B/~WR*: VF7.11, VH6.3, VH7.3, VH8.3, VH10.3, VH12.3, VH13.3, VH14.3
/video board/object/object RAM/CLK2: VA6.8, VG1.2, VG2.2, VG3.2
/video board/object/object RAM/CODE0: VE3.2, VE5.3, VE9.3
/video board/object/object RAM/CODE1: VE3.5, VE5.25, VE9.25
/video board/object/object RAM/CODE2: VE3.6, VE5.24, VE9.24
/video board/object/object RAM/CODE3: VE3.9, VE5.21, VE9.21
/video board/object/object RAM/CODE4: VE3.12, VE5.23, VE9.23
/video board/object/object RAM/CODE5: VE3.15, VE5.2, VE9.2
/video board/object/object RAM/CODE6: VE3.16, VE5.26, VE9.26
/video board/object/object RAM/CODE7: VE3.19, VE5.27, VE9.27
/video board/object/object RAM/CODE8: VE14.3, VF9.9
/video board/object/object RAM/D0: VE1.9, VF1.11, VF2.9
/video board/object/object RAM/D1: VE1.10, VF1.12, VF2.8
/video board/object/object RAM/D2: VE1.11, VF1.13, VF2.7
/video board/object/object RAM/D3: VE1.13, VF1.14, VF2.6
/video board/object/object RAM/D4: VE1.14, VF1.15, VF2.5
/video board/object/object RAM/D5: VE1.15, VF1.16, VF2.4
/video board/object/object RAM/D6: VE1.16, VF1.17, VF2.3
/video board/object/object RAM/D7: VE1.17, VF1.18, VF2.2
/video board/object/object RAM/DB0: VE3.3, VF2.11, VF3.3, VF4.3, VF9.3
/video board/object/object RAM/DB1: VE3.4, VF2.12, VF3.4, VF4.4, VF9.4
/video board/object/object RAM/DB2: VE3.7, VF2.13, VF3.7, VF4.5, VF9.7
/video board/object/object RAM/DB3: VE3.8, VF2.14, VF3.8, VF4.6, VF9.8
/video board/object/object RAM/DB4: VE3.13, VF2.15, VF3.13, VF5.3, VF9.13
/video board/object/object RAM/DB5: VE3.14, VF2.16, VF3.14, VF5.4, VF9.14
/video board/object/object RAM/DB6: VE3.17, VF2.17, VF3.17, VF5.5, VF9.17
/video board/object/object RAM/DB7: VE3.18, VF2.18, VF3.18, VF5.6, VF9.18
/video board/object/object RAM/G2_TC: VG2.15, VG3.7, VG3.10
/video board/object/object RAM/G3_TC: VG1.7, VG1.10, VG3.15
/video board/object/object RAM/NIBBLE: VA6.6, VF11.1
/video board/object/object RAM/OHFLIP*: VA6.4, VG9.15
/video board/object/object RAM/OVFLIP: VE13.2, VF9.19, VF13.2, VF13.9, VF13.12
/video board/object/object RAM/PAL0: VF9.2, VG9.3
/video board/object/object RAM/PAL1: VF9.5, VG9.4
/video board/object/object RAM/PAL2: VF9.6, VG9.6
/video board/object/object RAM/PREX8: VF9.15, VG1.3
/video board/object/object RAM/TC: VF4.15, VF5.7, VF5.10
/video board/object/object RAM/TC0: VA1.7, VA1.9, VA1.10, VA2.15
/video board/object/object RAM/TC1: VA1.15, VB1.7, VB1.9, VB1.10
/video board/object/object RAM/XOVER: VE13.11, VE19.5
/video board/object/object ROM/A0: VE5.10, VE9.10, VE13.8
/video board/object/object ROM/A1: VE5.9, VE9.9, VE13.6
/video board/object/object ROM/A2: VE5.8, VE9.8, VE13.3
/video board/object/object ROM/A3: VE5.7, VE9.7, VF13.11
/video board/object/object ROM/A4: VE5.6, VE9.6, VF13.8
/video board/object/object ROM/A5: VE5.5, VE9.5, VF13.6
/video board/object/object ROM/A6: VE5.4, VE9.4, VF13.3
/video board/object/object ROM/D0: VE5.11, VE9.11, VE11.3
/video board/object/object ROM/D1: VE5.12, VE9.12, VE11.4
/video board/object/object ROM/D2: VE5.13, VE9.13, VE11.7
/video board/object/object ROM/D3: VE5.15, VE9.15, VE11.8
/video board/object/object ROM/D4: VE5.16, VE9.16, VE11.13
/video board/object/object ROM/D5: VE5.17, VE9.17, VE11.14
/video board/object/object ROM/D6: VE5.18, VE9.18, VE11.17
/video board/object/object ROM/D7: VE5.19, VE9.19, VE11.18
/video board/object/object ROM/OHFLIP: VE13.5, VE13.9, VF9.16, VF13.5, VG9.14
/video board/object/object readout/DOT3: VC22.9, VD2.3, VE17.3, VG15.12
/video board/object/object readout/SEL: VF19.9, VH3.1, VI3.1
/video board/object/object readout/TC0: VH1.15, VI1.7, VI1.10
/video board/object/object readout/V8*: VE18.2, VF20.2, VF20.5, VG16.10, VG18.3
/video board/object/object readout/~CPUEN: VE16.8, VF15.2, VF16.5
/video board/object/object readout/~PE: VF18.5, VH1.9, VI1.9
/video board/object/~ATTR: VE3.11, VF15.14
/video board/object/~CASA: VG13.7, VH6.15, VH7.15, VH8.15, VH10.15, VH12.15, VH13.15, VH14.15
/video board/object/~CASB: VG13.4, VI6.15, VI7.15, VI8.15, VI10.15, VI12.15, VI13.15, VI14.15
/video board/object/~CLRA: VE17.9, VF6.1, VF6.4, VF6.10, VF7.13, VF14.10, VG6.1, VG6.4, VG6.10, VG6.13, VG13.1, VG14.10, VH4.1, VH5.1
/video board/object/~CLRB: VE17.8, VE17.12, VF6.13, VF7.1, VF7.4, VF7.10, VG7.1, VG7.4, VG7.10, VG7.13, VI4.1, VI5.1
/video board/object/~CODE: VF9.11, VF15.15
/video board/object/~FWR: VA5.8, VF6.12, VF7.12
/video board/object/~HB1: VA20.9, VD13.3, VE11.11
/video board/object/~HB4*: VD2.6, VF4.2, VF5.2
/video board/object/~PALCP: VF15.12, VG9.9
/video board/object/~RASA: VG13.12, VI6.4, VI7.4, VI8.4, VI10.4, VI12.4, VI13.4, VI14.4
/video board/object/~RASB: VG13.9, VH6.4, VH7.4, VH8.4, VH10.4, VH12.4, VH13.4, VH14.4
/video board/object/~START: VE18.8, VE19.2
/video board/object/~XCLR: VD2.8, VG1.9, VG2.9, VG3.9
/video board/object/~XLA: VF3.11, VF15.13
/video board/object/~XPE: VE17.5, VF4.9, VF5.9
/video board/object/~Y6*: VB2.3, VI17.7
/video board/scroll/scroll RAM/ATCK: VC7.11, VC14.8, VD9.11
/video board/scroll/scroll RAM/CODE0: VB9.4, VB14.4, VC7.2
/video board/scroll/scroll RAM/CODE1: VB9.3, VB14.3, VC7.5
/video board/scroll/scroll RAM/CODE2: VB9.25, VB14.25, VC7.6
/video board/scroll/scroll RAM/CODE3: VB9.24, VB14.24, VC7.9
/video board/scroll/scroll RAM/CODE4: VB9.21, VB14.21, VC7.12
/video board/scroll/scroll RAM/CODE5: VB9.23, VB14.23, VC7.15
/video board/scroll/scroll RAM/CODE6: VB9.2, VB14.2, VC7.16
/video board/scroll/scroll RAM/CODE7: VB9.26, VB14.26, VC7.19
/video board/scroll/scroll RAM/CODE8: VB9.27, VB14.27, VD9.12
/video board/scroll/scroll RAM/CODE9: VA14.13, VD9.15
/video board/scroll/scroll RAM/D0: VD6.9, VD7.3, VD9.3, VD11.11
/video board/scroll/scroll RAM/D1: VD6.10, VD7.4, VD9.4, VD11.12
/video board/scroll/scroll RAM/D2: VD6.11, VD7.7, VD9.7, VD11.13
/video board/scroll/scroll RAM/D3: VD6.13, VD7.8, VD9.8, VD11.14
/video board/scroll/scroll RAM/D4: VD6.14, VD7.13, VD9.13, VD11.15
/video board/scroll/scroll RAM/D5: VD6.15, VD7.14, VD9.14, VD11.16
/video board/scroll/scroll RAM/D6: VD6.16, VD7.17, VD9.17, VD11.17
/video board/scroll/scroll RAM/D7: VD6.17, VD7.18, VD9.18, VD11.18
/video board/scroll/scroll RAM/HFLIP: VB7.13, VC9.14, VD9.16
/video board/scroll/scroll RAM/HFLIP*: VA6.12, VC9.15
/video board/scroll/scroll RAM/HS4: VB3.10, VC5.6
/video board/scroll/scroll RAM/HS5: VB5.4, VC5.10
/video board/scroll/scroll RAM/HS6: VB5.1, VC5.13
/video board/scroll/scroll RAM/HS7: VB5.13, VC4.3
/video board/scroll/scroll RAM/HS8: VB5.10, VC4.6
/video board/scroll/scroll RAM/HX0: VC9.9, VD14.2, VE15.2
/video board/scroll/scroll RAM/HX1: VC14.3, VD14.7
/video board/scroll/scroll RAM/HX3: VC14.12, VD14.15
/video board/scroll/scroll RAM/SX0: VA4.2, VC6.4, VC11.13
/video board/scroll/scroll RAM/SX1: VA4.5, VB3.6, VC11.10
/video board/scroll/scroll RAM/SX2: VA4.6, VB3.2, VC11.4
/video board/scroll/scroll RAM/SX3: VA4.9, VB3.15, VC11.1
/video board/scroll/scroll RAM/SX4: VA4.12, VB3.11
/video board/scroll/scroll RAM/SX5: VA4.15, VB5.6
/video board/scroll/scroll RAM/VFLIP: VB6.2, VB6.5, VB6.9, VD9.19
/video board/scroll/scroll RAM/VS0: VB4.4, VB6.10
/video board/scroll/scroll RAM/VS1: VB4.1, VB6.4
/video board/scroll/scroll RAM/VS2: VB4.13, VB6.1
/video board/scroll/scroll RAM/VS3: VB4.10, VC4.10
/video board/scroll/scroll RAM/VS4: VC3.4, VC4.13
/video board/scroll/scroll RAM/VS5: VC3.1, VD4.3
/video board/scroll/scroll RAM/VS6: VC3.13, VD4.6
/video board/scroll/scroll RAM/VS7: VC3.10, VD4.10
/video board/scroll/scroll RAM/~HX0: VB15.11, VD14.3
/video board/scroll/scroll ROM/A0: VB7.8, VB9.10, VB14.10
/video board/scroll/scroll ROM/A1: VB7.6, VB9.9, VB14.9
/video board/scroll/scroll ROM/A2: VB6.8, VB9.8, VB14.8
/video board/scroll/scroll ROM/A3: VB6.6, VB9.7, VB14.7
/video board/scroll/scroll ROM/A4: VB6.3, VB9.6, VB14.6
/video board/scroll/scroll ROM/A5: VB6.11, VB9.5, VB14.5
/video board/scroll/scroll ROM/D0: VB9.11, VB14.11, VB15.3
/video board/scroll/scroll ROM/D1: VB9.12, VB14.12, VB15.4
/video board/scroll/scroll ROM/D2: VB9.13, VB14.13, VB15.7
/video board/scroll/scroll ROM/D3: VB9.15, VB14.15, VB15.8
/video board/scroll/scroll ROM/D4: VB9.16, VB14.16, VB15.13
/video board/scroll/scroll ROM/D5: VB9.17, VB14.17, VB15.14
/video board/scroll/scroll ROM/D6: VB9.18, VB14.18, VB15.17
/video board/scroll/scroll ROM/D7: VB9.19, VB14.19, VB15.18
/video board/scroll/~H8: VB5.12, VG20.6, VG21.4
/video board/timing/H0: VG19.5, VH17.10, VH18.13, VI18.7, VI18.10
/video board/timing/H1: VH17.12, VH18.10, VI18.14
/video board/timing/H2: VH17.14, VH18.4, VI18.13
/video board/timing/H3: VH17.6, VH18.1, VI18.12
/video board/timing/H4: VG21.3, VH17.4, VH19.13, VI18.11
/video board/timing/H5: VH17.2, VH19.10, VH20.4, VI19.14
/video board/timing/H6: VG20.3, VH19.4, VI17.10, VI19.13
/video board/timing/H7: VH19.1, VI17.12, VI19.12
/video board/timing/H8: VG18.9, VG20.5, VG22.2, VI19.11
/video board/timing/HBL*: VF20.13, VH22.12
/video board/timing/HCLK: VG19.3, VI17.4, VI18.2, VI19.2, VI20.6
/video board/timing/TCH: VG17.5, VG17.10, VI18.15, VI19.7, VI19.10
/video board/timing/VCLK: VG19.11, VG21.6, VI15.2, VI16.2
/video board/timing/VFX: VB17.10, VF21.10, VF22.2, VH20.12
/video board/timing/VTC: VI15.7, VI15.10, VI16.15
/video board/timing/X6: VI17.2, VI20.1, VI20.5
/video board/timing/Y6: VI17.14, VI20.3
/video board/timing/~Y6: VI17.6, VI20.2, VI20.8
/video board/watchdog/~POR: VE20.1, VI22.6
/video board/~CSSET: VE16.4, VE16.10, VE17.6
/video board/~HB1*: VD20.12, VF21.6
/video board/~HB2*: VB18.9, VF21.11
/video board/~HOVER: VF19.4, VF20.1, VF20.4, VG21.5
/video board/~HX3: VC6.9, VC15.12, VD14.14
/video board/~OBJCS: VA5.2, VA22.5, VC1.1, VC2.1, VD3.1, VF1.19, VF16.6
/video board/~OBJMX: VE20.11, VF16.1, VF16.4, VG15.9
/video board/~PH1: VB17.1, VC16.1, VC17.1, VD20.9, VE22.1, VF22.6
/video board/~SCRCS: VA22.4, VC15.4, VD11.19, VD13.8
/video board/~SCRSEL: VC4.1, VC5.1, VC6.8, VD4.1, VE19.12
/video board/~SCRXM: VA3.11, VA14.5
/video board/~SCRX: VA4.11, VA14.4
/video board/~SCRY: VA14.6, VC13.3
/video board/~SSDSET: VE21.4, VF22.10
/~MWAIT: E1.24, VA11.8
/~SWAIT: H1.24, VA11.6
/~VBL: H4.3, H4.11, VA5.9, VG21.8, VH21.1
GND: B1.7, B2.7, B3.8, B4.8, B5.7, B7.7, B11.8, B12.8, B19.14, B19.20, B19.22, C1.14, C2.14, C4.14, C6.8, C7.2, C7.10, C7.15, C8.2, C8.10, C8.15, C9.2, C9.10, C9.15, C10.2, C10.10, C10.15, C11.7, C15.11, D6.8, D7.4, D7.6, D7.10, D7.11, D7.15, D8.4, D8.6, D8.10, D8.11, D8.15, D9.4, D9.6, D9.10, D9.11, D9.15, D10.4, D10.6, D10.10, D10.11, D10.15, D12.8, D14.14, D14.22, D17.2, D17.9, D17.12, DA1.7, DA2.7, DA3.7, DA4.7, DA5.2, DA5.7, DA5.12, DB1.7, DB2.10, DB3.1, DC1.7, DC2.10, DC3.1, E1.29, E2.7, E3.12, E5.10, E6.10, E10.7, E13.8, E14.8, E15.8, E16.8, E17.7, F4.7, F12.1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
unnamed: B1.3, C5.10
unnamed: B1.11, C5.11
unnamed: B2.3, C5.7
unnamed: B2.11, C5.9
unnamed: B19.11, VB21.3
unnamed: B19.12, VB21.4
unnamed: B19.13, VB21.7
unnamed: B19.15, VB21.8
unnamed: B19.16, VB21.13
unnamed: B19.17, VB21.14
unnamed: B19.18, VB21.17
unnamed: B19.19, VB21.18
unnamed: C5.15, C6.15
unnamed: C5.14, D6.15
unnamed: C6.1, D5.15
unnamed: B7.6, C7.6
unnamed: C7.4, D7.2
unnamed: C7.7, D7.8
unnamed: C7.9, D7.13
unnamed: B7.4, C8.6
unnamed: C8.4, D8.2
unnamed: C8.7, D8.8
unnamed: C8.9, D8.13
unnamed: B5.8, C9.6
unnamed: C9.4, D9.2
unnamed: C9.7, D9.8
unnamed: C9.9, D9.13
unnamed: B5.10, C10.6
unnamed: C10.4, D10.2
unnamed: C10.7, D10.8
unnamed: C10.9, D10.13
unnamed: C11.5, C11.13
unnamed: C11.8, C11.12
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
